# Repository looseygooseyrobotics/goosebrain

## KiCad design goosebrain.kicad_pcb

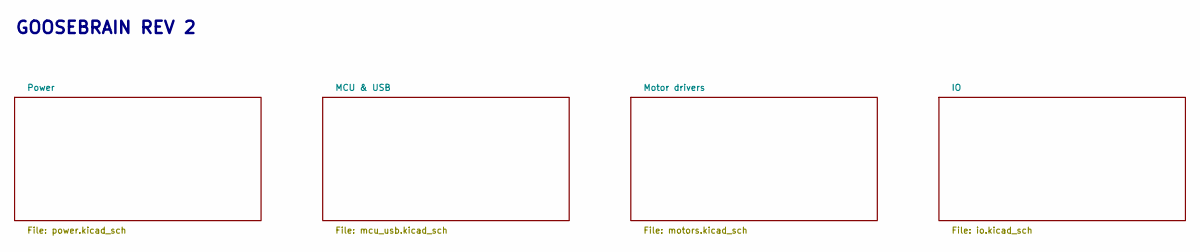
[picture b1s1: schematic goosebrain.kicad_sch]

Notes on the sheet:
GOOSEBRAIN REV 2

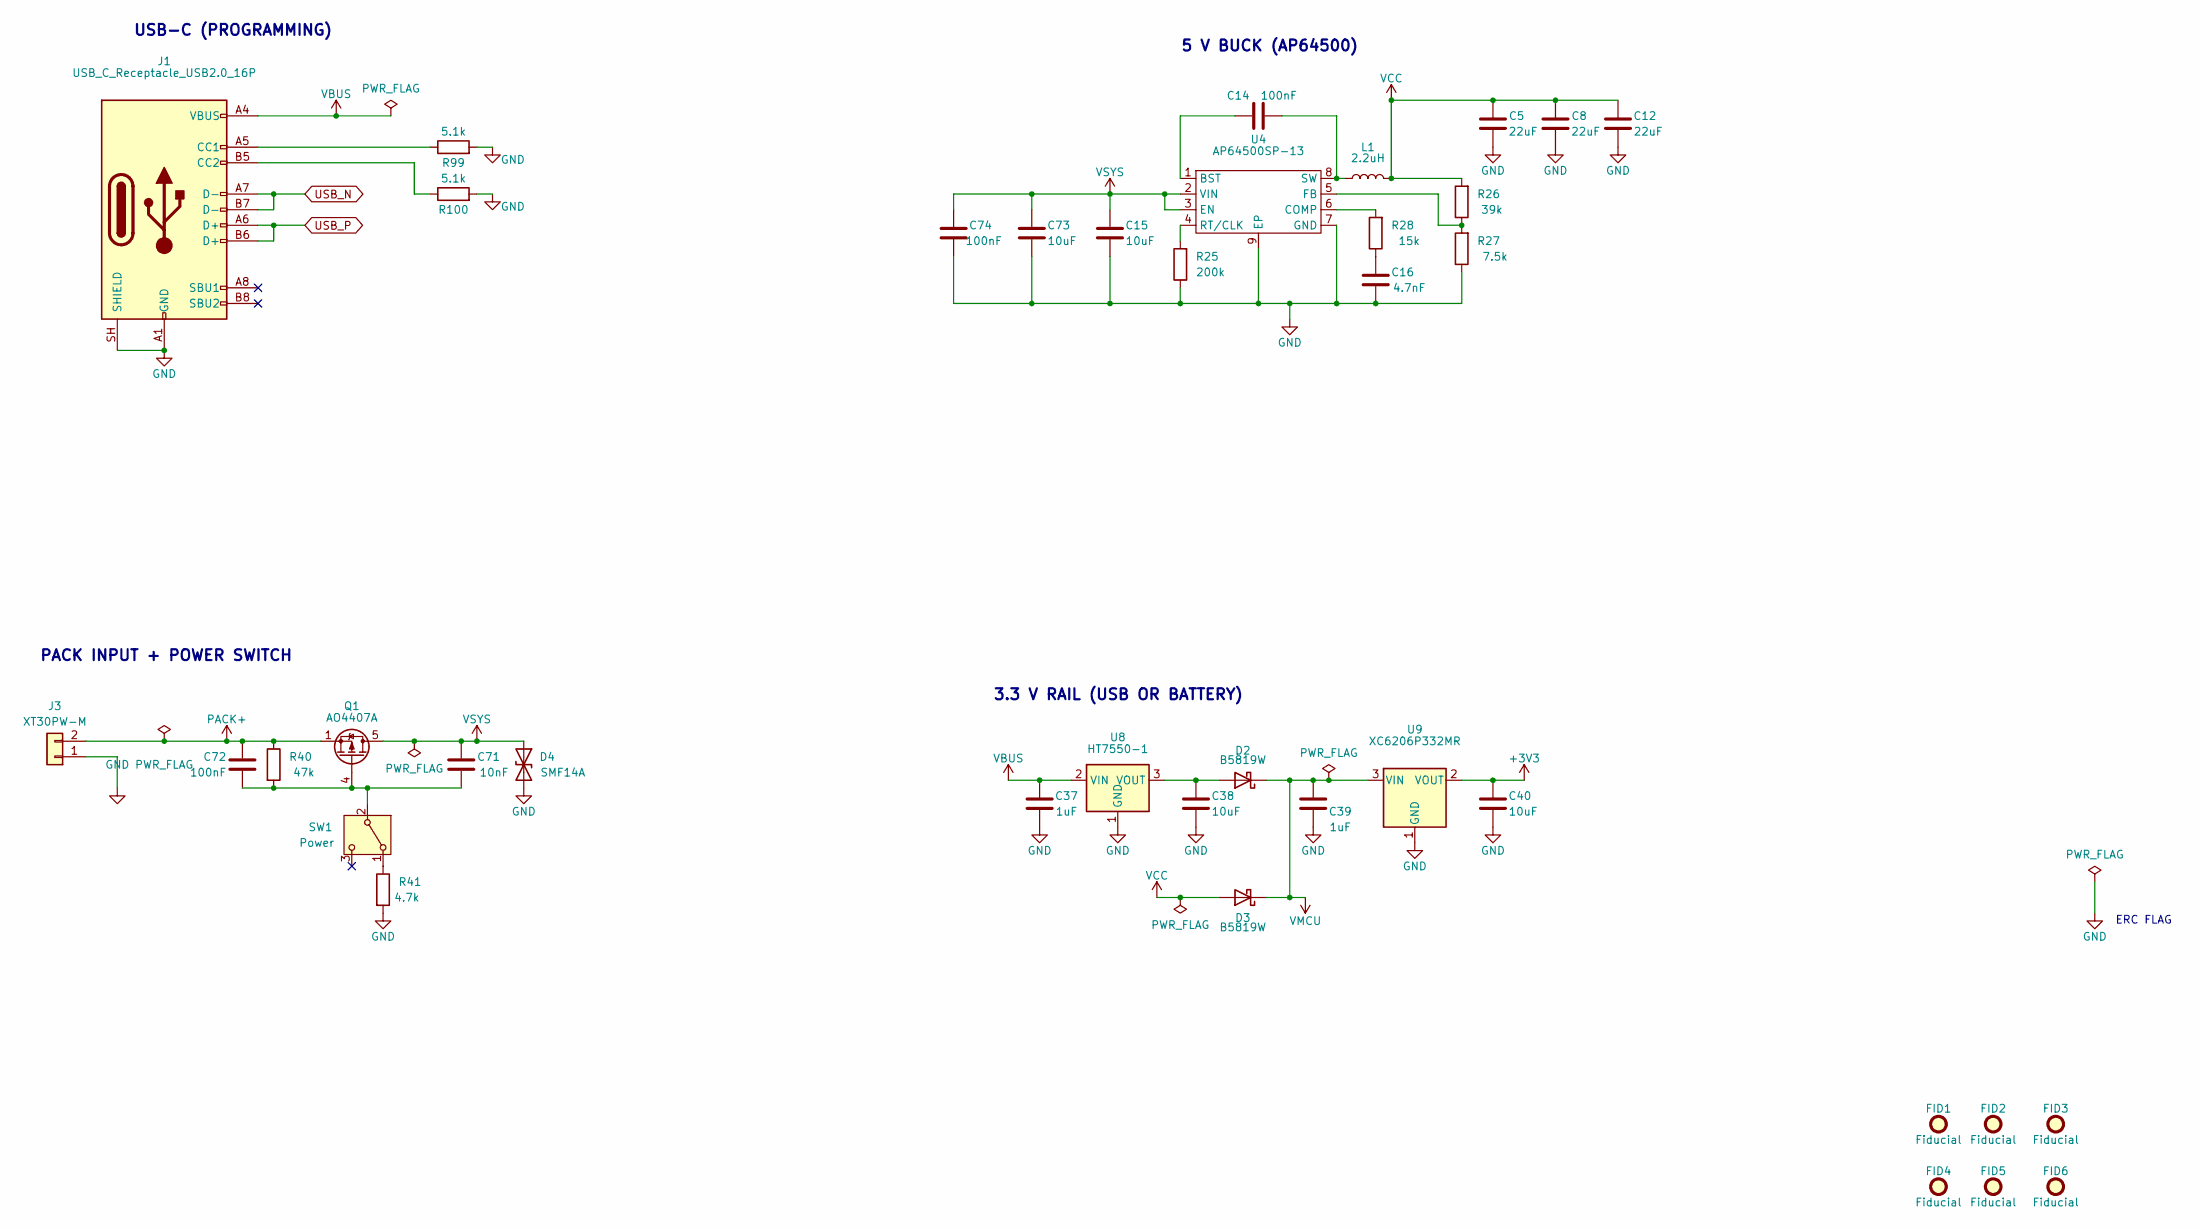
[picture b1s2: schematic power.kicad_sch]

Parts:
C5, C8, C12: 22uF; C_1206_3216Metric; MPN CL31A226KPHNNNE; LCSC Part # C5672
C14, C72: 100nF; C_0805_2012Metric; MPN CC0805KRX7R9BB104; LCSC Part # C49678
C15, C73: 10uF; C_0805_2012Metric; MPN CL21A106KAYNNNE; LCSC Part # C15850
C16: 4.7nF; C_0402_1005Metric; MPN 0402B472K500NT; LCSC Part # C1538
C37: 1uF; C_0603_1608Metric; MPN CL10A105KB8NNNC; LCSC Part # C15849
C38, C40: 10uF; C_0603_1608Metric; MPN CL10A106KP8NNNC; LCSC Part # C19702
C39: 1uF; C_0402_1005Metric; MPN CL05A105KA5NQNC; LCSC Part # C52923
C71: 10nF; C_0402_1005Metric; MPN CL05B103KB5NNNC; LCSC Part # C15195
C74: 100nF; C_0402_1005Metric; MPN CL05B104KB54PNC; LCSC Part # C307331
D2, D3: B5819W; D_SOD-123; MPN B5819W; LCSC Part # C64885
D4: SMF14A; D_SMF; MPN SMF14A; LCSC Part # C207256
FID1, FID2, FID3, FID4, FID5, FID6: Fiducial; Fiducial_1mm_Mask2mm
J1: USB_C_Receptacle_USB2.0_16P; USB_C_Receptacle_ShouHan_TYPE-C16PIN; MPN TYPE-C16PIN; LCSC Part # C393939
J3: XT30PW-M; AMASS_XT30PW-M_1x02_P2.50mm_Horizontal; MPN XT30PW-M30.G.Y; LCSC Part # C431092
L1: 2.2uH; L_ZengYi_HMS0530; MPN HMS0530-2R2M; LCSC Part # C18734448
Q1: AO4407A; SOIC-8_3.9x4.9mm_P1.27mm; MPN AO4407A; LCSC Part # C2841482
R25: 200k; R_0402_1005Metric; MPN 0402WGF2003TCE; LCSC Part # C25764
R26: 39k; R_0402_1005Metric; MPN 0402WGF3902TCE; LCSC Part # C25783
R27: 7.5k; R_0402_1005Metric; MPN 0402WGF7501TCE; LCSC Part # C25918
R28: 15k; R_0402_1005Metric; MPN 0402WGF1502TCE; LCSC Part # C25756
R40: 47k; R_0402_1005Metric; MPN 0402WGF4702TCE; LCSC Part # C25792
R41: 4.7k; R_0402_1005Metric; MPN 0402WGF4701TCE; LCSC Part # C25900
R99, R100: 5.1k; R_0402_1005Metric; MPN 0402WGF5101TCE; LCSC Part # C25905
SW1: Power; SW_SPDT_ShouHan_SK12D07VG4; MPN SK12D07VG4; LCSC Part # C393937
U4: AP64500SP-13; Diodes_SO-8EP; MPN AP64500SP-13; LCSC Part # C2070920
U8: HT7550-1; SOT-89-3; MPN HT7550-1; LCSC Part # C16106
U9: XC6206P332MR; SOT-23-3; MPN XC6206P332MR-G; LCSC Part # C5446

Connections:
+3V3: C40.1, U9.2 (VOUT); also elsewhere on the board
/Power/CC1: J1.A5 (CC1), R99.1
/Power/CC2: J1.B5 (CC2), R100.1
GND: C5.2, C8.2, C12.2, C15.1, C16.1, C37.2, C38.2, C39.2, C40.2, C73.1, C74.1, D4.2 (A2), J1.A1 (GND), J1.A12 (GND), J1.B1 (GND), J1.B12 (GND), J1.SH (SHIELD), J3.1, R25.1, R27.1, R41.2, R99.2, R100.2, U4.7 (GND), U4.9 (EP), U8.1 (GND), U9.1 (GND); also elsewhere on the board
unnamed: C16.2, R28.1
unnamed: C38.1, D2.2 (A), U8.3 (VOUT)
unnamed: C71.1, C72.2, Q1.4 (G), R40.2, SW1.2 (B)
unnamed: R41.1, SW1.1 (A)
unnamed: C14.2, U4.1 (BST)
unnamed: R28.2, U4.6 (COMP)
unnamed: R26.1, R27.2, U4.5 (FB)
unnamed: R25.2, U4.4 (RT/CLK)
unnamed: C14.1, L1.1, U4.8 (SW)
PACK+: C72.1, J3.2, Q1.1 (S), Q1.2 (S), Q1.3 (S), R40.1
VBUS: C37.1, J1.A4 (VBUS), J1.A9 (VBUS), J1.B4 (VBUS), J1.B9 (VBUS), U8.2 (VIN)
VCC: C5.1, C8.1, C12.1, D3.2 (A), L1.2, R26.2; also elsewhere on the board
VMCU: C39.1, D2.1 (K), D3.1 (K), U9.3 (VIN); also elsewhere on the board
VSYS: C15.2, C71.2, C73.2, C74.2, D4.1 (A1), Q1.5 (D), Q1.6 (D), Q1.7 (D), Q1.8 (D), U4.2 (VIN), U4.3 (EN); also elsewhere on the board

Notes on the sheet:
ERC FLAG
3.3 V RAIL (USB OR BATTERY)
5 V BUCK (AP64500)
USB-C (PROGRAMMING)
PACK INPUT + POWER SWITCH

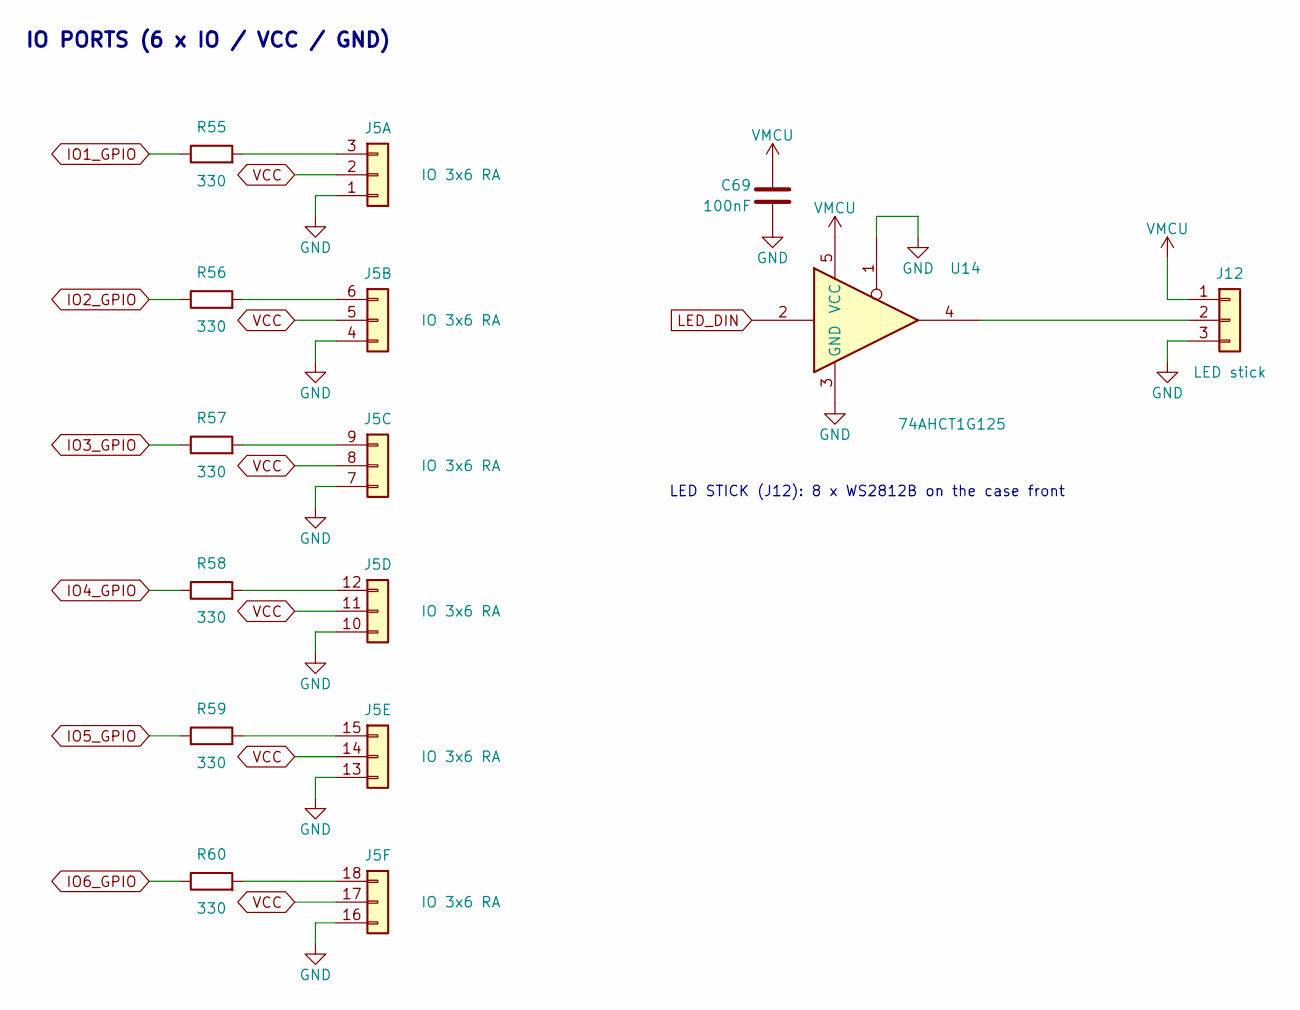
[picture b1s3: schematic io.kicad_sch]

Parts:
C69: 100nF; C_0402_1005Metric; MPN CL05B104KO5NNNC; LCSC Part # C1525
J5: IO 3x6 RA; PinHeader_3x06_P2.54mm_Horizontal_WingTAT; MPN 2011-3X06G00RB; LCSC Part # C51953246
J12: LED stick; JST_PH_B3B-PH-K_1x03_P2.00mm_Vertical; MPN B3B-PH-K-S(LF)(SN); LCSC Part # C131339
R55, R56, R57, R58, R59, R60: 330; R_0402_1005Metric; MPN 0402WGF3300TCE; LCSC Part # C25104
U14: 74AHCT1G125; SOT-23-5; MPN SN74AHCT1G125DBVR; LCSC Part # C20617903

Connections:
GND: C69.2, J5.1 (GND), J5.4 (GND), J5.7 (GND), J5.10 (GND), J5.13 (GND), J5.16 (GND), J12.3, U14.1, U14.3 (GND); also elsewhere on the board
IO1_GPIO: R55.1; also elsewhere on the board
IO2_GPIO: R56.1; also elsewhere on the board
IO3_GPIO: R57.1; also elsewhere on the board
IO4_GPIO: R58.1; also elsewhere on the board
IO5_GPIO: R59.1; also elsewhere on the board
IO6_GPIO: R60.1; also elsewhere on the board
LED_DIN: U14.2; also elsewhere on the board
unnamed: J5.3 (SIG), R55.2
unnamed: J5.6 (SIG), R56.2
unnamed: J5.9 (SIG), R57.2
unnamed: J5.12 (SIG), R58.2
unnamed: J5.15 (SIG), R59.2
unnamed: J5.18 (SIG), R60.2
unnamed: J12.2, U14.4
VCC: J5.2 (5V), J5.5 (5V), J5.8 (5V), J5.11 (5V), J5.14 (5V), J5.17 (5V); also elsewhere on the board
VMCU: C69.1, J12.1, U14.5 (VCC); also elsewhere on the board

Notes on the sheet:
LED STICK (J12): 8 x WS2812B on the case front
IO PORTS (6 x IO / VCC / GND)

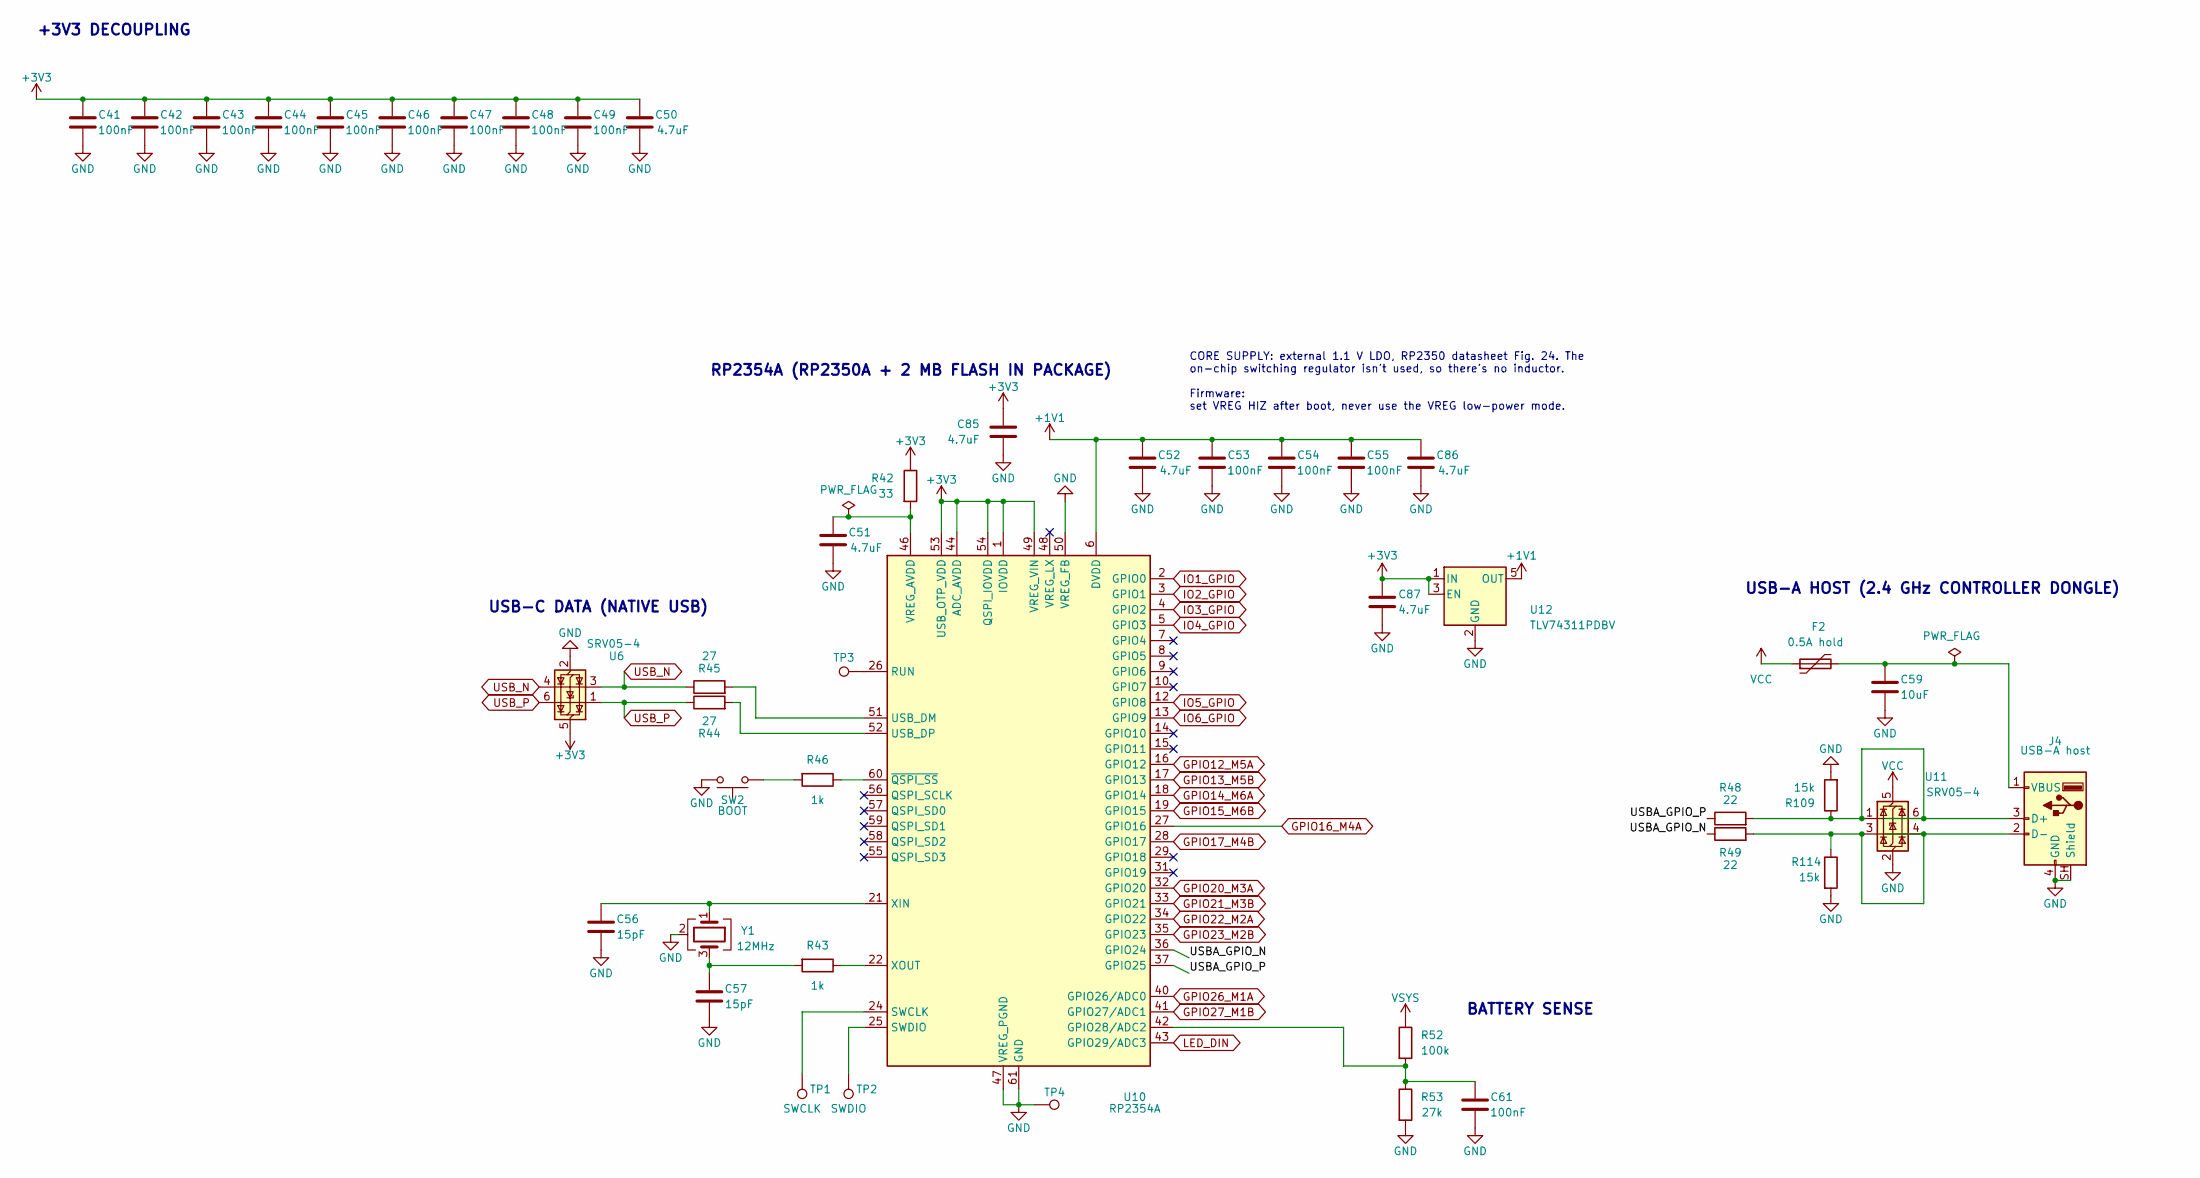
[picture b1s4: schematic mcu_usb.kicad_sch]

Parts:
C41, C42, C43, C44, C45, C46, C47, C48, C49, C53, C54, C55, C61: 100nF; C_0402_1005Metric; MPN CL05B104KO5NNNC; LCSC Part # C1525
C50, C51, C52, C85, C86, C87: 4.7uF; C_0402_1005Metric; MPN CL05A475MP5NRNC; LCSC Part # C23733
C56, C57: 15pF; C_0402_1005Metric; MPN 0402CG150J500NT; LCSC Part # C1548
C59: 10uF; C_0805_2012Metric; MPN CL21A106KAYNNNE; LCSC Part # C15850
F2: 0.5A hold; Fuse_1206_3216Metric; MPN JK-nSMD050-16; LCSC Part # C2680506
J4: USB-A host; USB_A_ShouHan_AF90_WJDG; MPN AF 90 WJDG; LCSC Part # C456018
R42: 33; R_0402_1005Metric; MPN 0402WGF330JTCE; LCSC Part # C25105
R43, R46: 1k; R_0402_1005Metric; MPN 0402WGF1001TCE; LCSC Part # C11702
R44, R45: 27; R_0603_1608Metric; MPN 0603WAF270JT5E; LCSC Part # C25190
R48, R49: 22; R_0402_1005Metric; MPN 0402WGF220JTCE; LCSC Part # C25092
R52: 100k; R_0402_1005Metric; MPN 0402WGF1003TCE; LCSC Part # C25741
R53: 27k; R_0402_1005Metric; MPN 0402WGF2702TCE; LCSC Part # C25771
R109, R114: 15k; R_0402_1005Metric; MPN 0402WGF1502TCE; LCSC Part # C25756
SW2: BOOT; SW_Push_1P1T-MP_NO_Horizontal_Alps_SKRTLAE010_JLC; MPN SKRTLAE010; LCSC Part # C110293
TP1: SWCLK; TestPoint_Pad_D1.0mm
TP2: SWDIO; TestPoint_Pad_D1.0mm
TP3: RUN; TestPoint_Pad_D1.0mm
TP4: GND; TestPoint_Pad_D1.0mm
U6, U11: SRV05-4; SOT-23-6; MPN SRV05-4; LCSC Part # C7420376
U10: RP2354A; QFN-60-1EP_7x7mm_P0.4mm_EP3.4x3.4mm; MPN RP2354A; LCSC Part # C41378174
U12: TLV74311PDBV; SOT-23-5; MPN TLV74311PDBVR; LCSC Part # C485147
Y1: 12MHz; Crystal_SMD_3225-4Pin_3.2x2.5mm; MPN ABM8-272-T3; LCSC Part # C20625731

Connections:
+1V1: C52.1, C53.1, C54.1, C55.1, C86.1, U10.6 (DVDD), U10.23 (DVDD), U10.39 (DVDD), U12.5 (OUT)
+3V3: C41.1, C42.1, C43.1, C44.1, C45.1, C46.1, C47.1, C48.1, C49.1, C50.1, C85.1, C87.1, R42.1, U6.5 (VP), U10.1 (IOVDD), U10.11 (IOVDD), U10.20 (IOVDD), U10.30 (IOVDD), U10.38 (IOVDD), U10.44 (ADC_AVDD), U10.45 (IOVDD), U10.49 (VREG_VIN), U10.53 (USB_OTP_VDD), U10.54 (QSPI_IOVDD), U12.1 (IN), U12.3 (EN); also elsewhere on the board
/MCU & USB/BAT_SENSE: C61.1, R52.2, R53.1, U10.42 (GPIO28/ADC2)
/MCU & USB/RUN: TP3.1 (1_1), U10.26 (RUN)
/MCU & USB/USBA_GPIO_N: R49.1, U10.36 (GPIO24)
/MCU & USB/USBA_GPIO_P: R48.1, U10.37 (GPIO25)
/MCU & USB/USBA_N: J4.2 (D-), R49.2, R114.1, U11.3 (IO2), U11.4 (IO3)
/MCU & USB/USBA_P: J4.3 (D+), R48.2, R109.1, U11.1 (IO1), U11.6 (IO4)
GND: C41.2, C42.2, C43.2, C44.2, C45.2, C46.2, C47.2, C48.2, C49.2, C50.2, C51.2, C52.2, C53.2, C54.2, C55.2, C56.2, C57.2, C59.2, C61.2, C85.2, C86.2, C87.2, J4.4 (GND), J4.SH (Shield), R53.2, R109.2, R114.2, SW2.2, TP4.1 (1_1), U6.2 (VN), U10.47 (VREG_PGND), U10.50 (VREG_FB), U10.61 (GND), U11.2 (VN), U12.2 (GND), Y1.2 (G), Y1.4 (G); also elsewhere on the board
GPIO12_M5A: U10.16 (GPIO12); also elsewhere on the board
GPIO13_M5B: U10.17 (GPIO13); also elsewhere on the board
GPIO14_M6A: U10.18 (GPIO14); also elsewhere on the board
GPIO15_M6B: U10.19 (GPIO15); also elsewhere on the board
GPIO16_M4A: U10.27 (GPIO16); also elsewhere on the board
GPIO17_M4B: U10.28 (GPIO17); also elsewhere on the board
GPIO20_M3A: U10.32 (GPIO20); also elsewhere on the board
GPIO21_M3B: U10.33 (GPIO21); also elsewhere on the board
GPIO22_M2A: U10.34 (GPIO22); also elsewhere on the board
GPIO23_M2B: U10.35 (GPIO23); also elsewhere on the board
GPIO26_M1A: U10.40 (GPIO26/ADC0); also elsewhere on the board
GPIO27_M1B: U10.41 (GPIO27/ADC1); also elsewhere on the board
IO1_GPIO: U10.2 (GPIO0); also elsewhere on the board
IO2_GPIO: U10.3 (GPIO1); also elsewhere on the board
IO3_GPIO: U10.4 (GPIO2); also elsewhere on the board
IO4_GPIO: U10.5 (GPIO3); also elsewhere on the board
IO5_GPIO: U10.12 (GPIO8); also elsewhere on the board
IO6_GPIO: U10.13 (GPIO9); also elsewhere on the board
LED_DIN: U10.43 (GPIO29/ADC3); also elsewhere on the board
unnamed: C57.1, R43.2, Y1.3
unnamed: C59.1, F2.2, J4.1 (VBUS)
unnamed: R46.2, SW2.1
unnamed: TP1.1 (1_1), U10.24 (SWCLK)
unnamed: TP2.1 (1_1), U10.25 (SWDIO)
unnamed: C51.1, R42.2, U10.46 (VREG_AVDD)
unnamed: C56.1, U10.21 (XIN), Y1.1
unnamed: R43.1, U10.22 (XOUT)
unnamed: R46.1, U10.60 (~QSPI_SS)
VCC: F2.1, U11.5 (VP); also elsewhere on the board
VSYS: R52.1; also elsewhere on the board

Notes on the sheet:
RP2354A (RP2350A + 2 MB FLASH IN PACKAGE)
+3V3 DECOUPLING
CORE SUPPLY: external 1.1 V LDO, RP2350 datasheet Fig. 24. The on-chip switching regulator isn't used, so there's no inductor. Firmware: set VREG HIZ after boot, never use the VREG low-power mode.
BATTERY SENSE
USB-C DATA (NATIVE USB)
USB-A HOST (2.4 GHz CONTROLLER DONGLE)

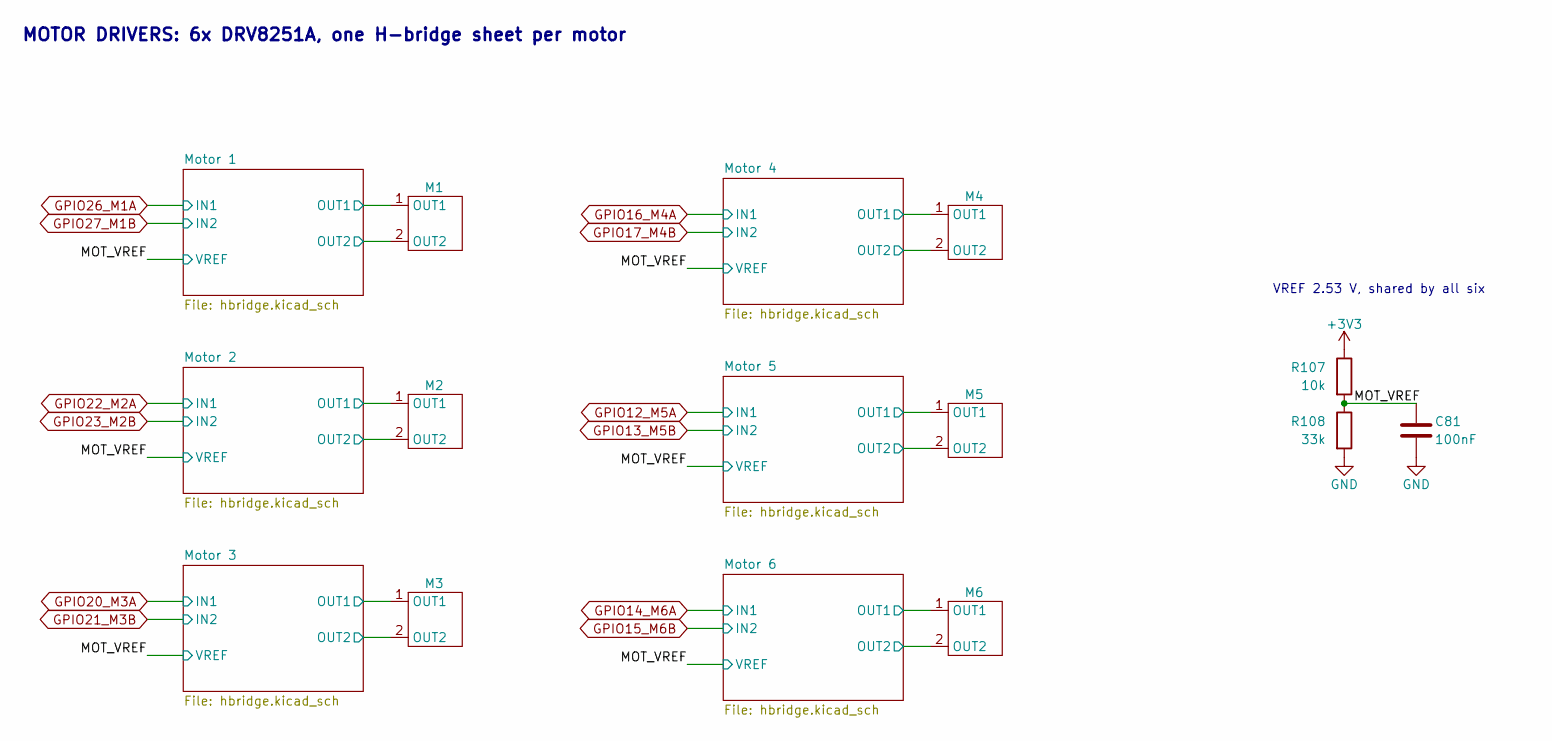
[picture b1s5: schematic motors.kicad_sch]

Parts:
C81: 100nF; C_0402_1005Metric; MPN CL05B104KO5NNNC; LCSC Part # C1525
M1, M2, M3, M4, M5, M6: JST_PH_S2B-PH-K_1x02_P2.00mm_Horizontal; MPN S2B-PH-K-S(LF)(SN); LCSC Part # C173752
R107: 10k; R_0402_1005Metric; MPN 0402WGF1002TCE; LCSC Part # C25744
R108: 33k; R_0402_1005Metric; MPN 0402WGF3302TCE; LCSC Part # C25779

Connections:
+3V3: R107.1; also elsewhere on the board
/Motor drivers/MOT_VREF: C81.1, R107.2, R108.1; also elsewhere on the board
/Motor drivers/Motor 1/OUT1: M1.1 (OUT1); also elsewhere on the board
/Motor drivers/Motor 1/OUT2: M1.2 (OUT2); also elsewhere on the board
/Motor drivers/Motor 2/OUT1: M2.1 (OUT1); also elsewhere on the board
/Motor drivers/Motor 2/OUT2: M2.2 (OUT2); also elsewhere on the board
/Motor drivers/Motor 3/OUT1: M3.1 (OUT1); also elsewhere on the board
/Motor drivers/Motor 3/OUT2: M3.2 (OUT2); also elsewhere on the board
/Motor drivers/Motor 4/OUT1: M4.1 (OUT1); also elsewhere on the board
/Motor drivers/Motor 4/OUT2: M4.2 (OUT2); also elsewhere on the board
/Motor drivers/Motor 5/OUT1: M5.1 (OUT1); also elsewhere on the board
/Motor drivers/Motor 5/OUT2: M5.2 (OUT2); also elsewhere on the board
/Motor drivers/Motor 6/OUT1: M6.1 (OUT1); also elsewhere on the board
/Motor drivers/Motor 6/OUT2: M6.2 (OUT2); also elsewhere on the board
GND: C81.2, R108.2; also elsewhere on the board

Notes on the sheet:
VREF 2.53 V, shared by all six
MOTOR DRIVERS: 6x DRV8251A, one H-bridge sheet per motor

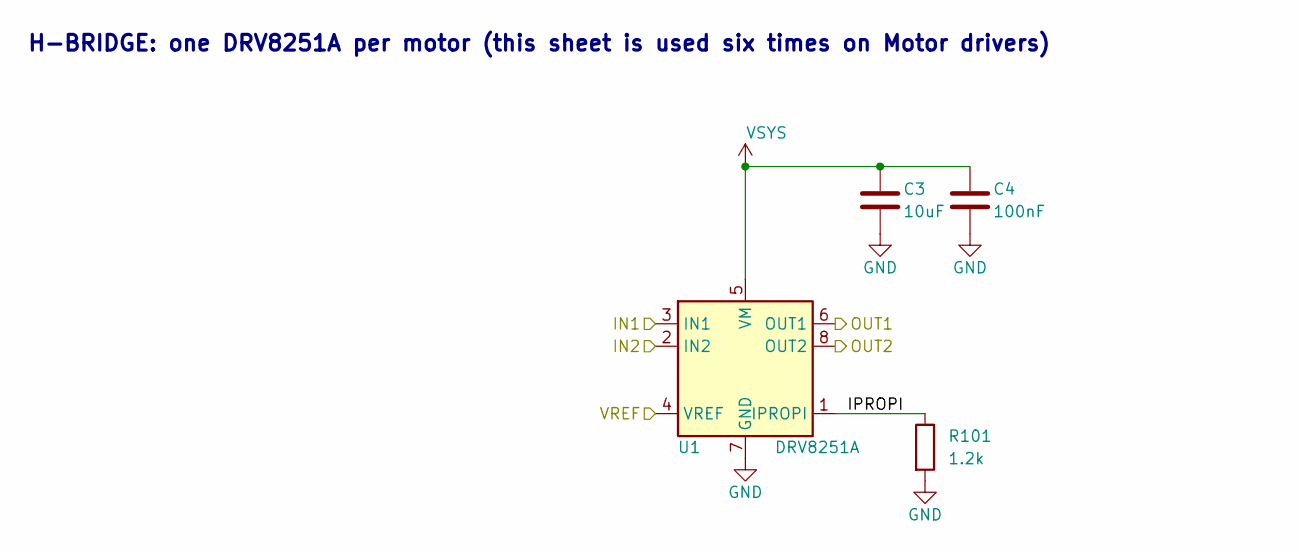
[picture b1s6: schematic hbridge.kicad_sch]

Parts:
C3: 10uF; C_0805_2012Metric; MPN CL21A106KAYNNNE; LCSC Part # C15850
C4: 100nF; C_0805_2012Metric; MPN CC0805KRX7R9BB104; LCSC Part # C49678
R101: 1.2k; R_0402_1005Metric; MPN 0402WGF1201TCE; LCSC Part # C25862
U1: DRV8251A; Texas_HTSOP-8-1EP_3.9x4.9mm_P1.27mm_EP2.95x4.9mm_Mask2.4x3.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; MPN DRV8251ADDAR; LCSC Part # C5218844

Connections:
/Motor drivers/MOT_VREF: U1.4 (VREF); also elsewhere on the board
/Motor drivers/Motor 1/IPROPI: R101.1, U1.1 (IPROPI)
/Motor drivers/Motor 1/OUT1: U1.6 (OUT1); also elsewhere on the board
/Motor drivers/Motor 1/OUT2: U1.8 (OUT2); also elsewhere on the board
GND: C3.2, C4.2, R101.2, U1.7 (GND), U1.9 (GND); also elsewhere on the board
GPIO26_M1A: U1.3 (IN1); also elsewhere on the board
GPIO27_M1B: U1.2 (IN2); also elsewhere on the board
VSYS: C3.1, C4.1, U1.5 (VM); also elsewhere on the board

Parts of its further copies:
C6, C10, C75, C77, C79: 10uF; C_0805_2012Metric; MPN CL21A106KAYNNNE; LCSC Part # C15850
C7, C11, C76, C78, C80: 100nF; C_0805_2012Metric; MPN CC0805KRX7R9BB104; LCSC Part # C49678
R102, R103, R104, R105, R106: 1.2k; R_0402_1005Metric; MPN 0402WGF1201TCE; LCSC Part # C25862
U2, U3, U15, U16, U17: DRV8251A; Texas_HTSOP-8-1EP_3.9x4.9mm_P1.27mm_EP2.95x4.9mm_Mask2.4x3.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; MPN DRV8251ADDAR; LCSC Part # C5218844

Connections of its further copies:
/Motor drivers/MOT_VREF: U2.4 (VREF), U3.4 (VREF), U15.4 (VREF), U16.4 (VREF), U17.4 (VREF); also elsewhere on the board
/Motor drivers/Motor 2/IPROPI: R102.1, U15.1 (IPROPI)
/Motor drivers/Motor 2/OUT1: U15.6 (OUT1); also elsewhere on the board
/Motor drivers/Motor 2/OUT2: U15.8 (OUT2); also elsewhere on the board
/Motor drivers/Motor 3/IPROPI: R103.1, U2.1 (IPROPI)
/Motor drivers/Motor 3/OUT1: U2.6 (OUT1); also elsewhere on the board
/Motor drivers/Motor 3/OUT2: U2.8 (OUT2); also elsewhere on the board
/Motor drivers/Motor 4/IPROPI: R104.1, U16.1 (IPROPI)
/Motor drivers/Motor 4/OUT1: U16.6 (OUT1); also elsewhere on the board
/Motor drivers/Motor 4/OUT2: U16.8 (OUT2); also elsewhere on the board
/Motor drivers/Motor 5/IPROPI: R105.1, U3.1 (IPROPI)
/Motor drivers/Motor 5/OUT1: U3.6 (OUT1); also elsewhere on the board
/Motor drivers/Motor 5/OUT2: U3.8 (OUT2); also elsewhere on the board
/Motor drivers/Motor 6/IPROPI: R106.1, U17.1 (IPROPI)
/Motor drivers/Motor 6/OUT1: U17.6 (OUT1); also elsewhere on the board
/Motor drivers/Motor 6/OUT2: U17.8 (OUT2); also elsewhere on the board
GND: C6.2, C7.2, C10.2, C11.2, C75.2, C76.2, C77.2, C78.2, C79.2, C80.2, R102.2, R103.2, R104.2, R105.2, R106.2, U2.7 (GND), U2.9 (GND), U3.7 (GND), U3.9 (GND), U15.7 (GND), U15.9 (GND), U16.7 (GND), U16.9 (GND), U17.7 (GND), U17.9 (GND); also elsewhere on the board
GPIO12_M5A: U3.3 (IN1); also elsewhere on the board
GPIO13_M5B: U3.2 (IN2); also elsewhere on the board
GPIO14_M6A: U17.3 (IN1); also elsewhere on the board
GPIO15_M6B: U17.2 (IN2); also elsewhere on the board
GPIO16_M4A: U16.3 (IN1); also elsewhere on the board
GPIO17_M4B: U16.2 (IN2); also elsewhere on the board
GPIO20_M3A: U2.3 (IN1); also elsewhere on the board
GPIO21_M3B: U2.2 (IN2); also elsewhere on the board
GPIO22_M2A: U15.3 (IN1); also elsewhere on the board
GPIO23_M2B: U15.2 (IN2); also elsewhere on the board
VSYS: C6.1, C7.1, C10.1, C11.1, C75.1, C76.1, C77.1, C78.1, C79.1, C80.1, U2.5 (VM), U3.5 (VM), U15.5 (VM), U16.5 (VM), U17.5 (VM); also elsewhere on the board

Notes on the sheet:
H-BRIDGE: one DRV8251A per motor (this sheet is used six times on Motor drivers)

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
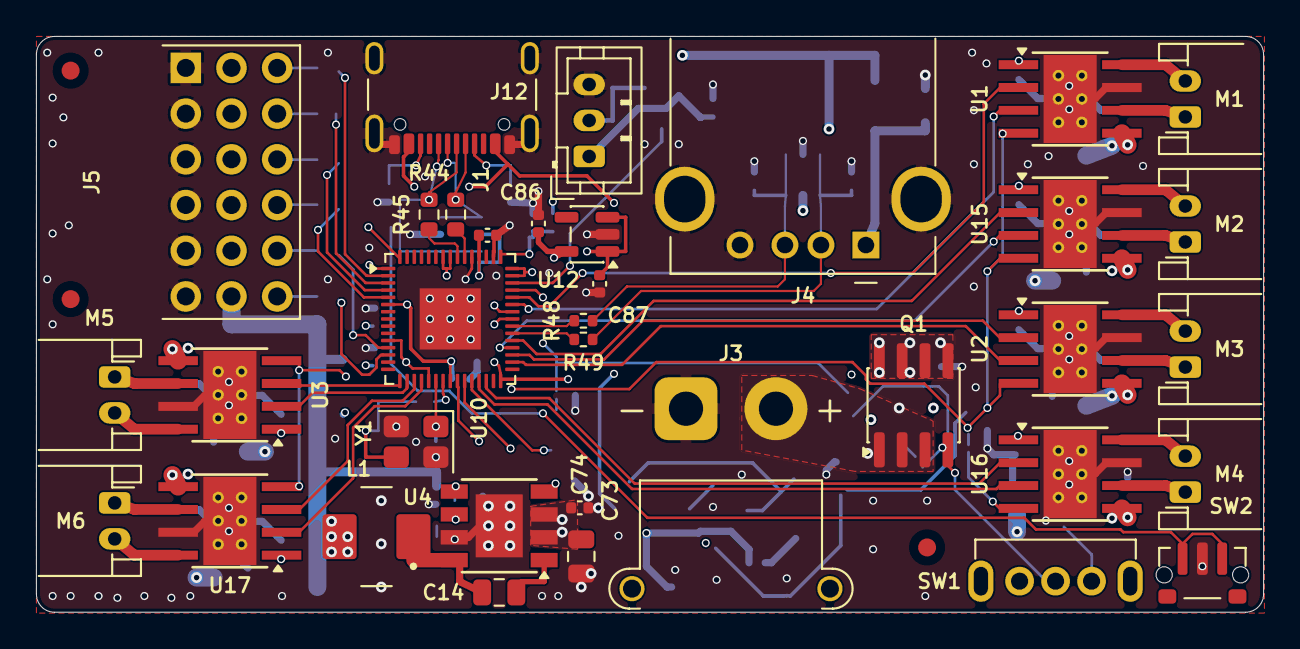
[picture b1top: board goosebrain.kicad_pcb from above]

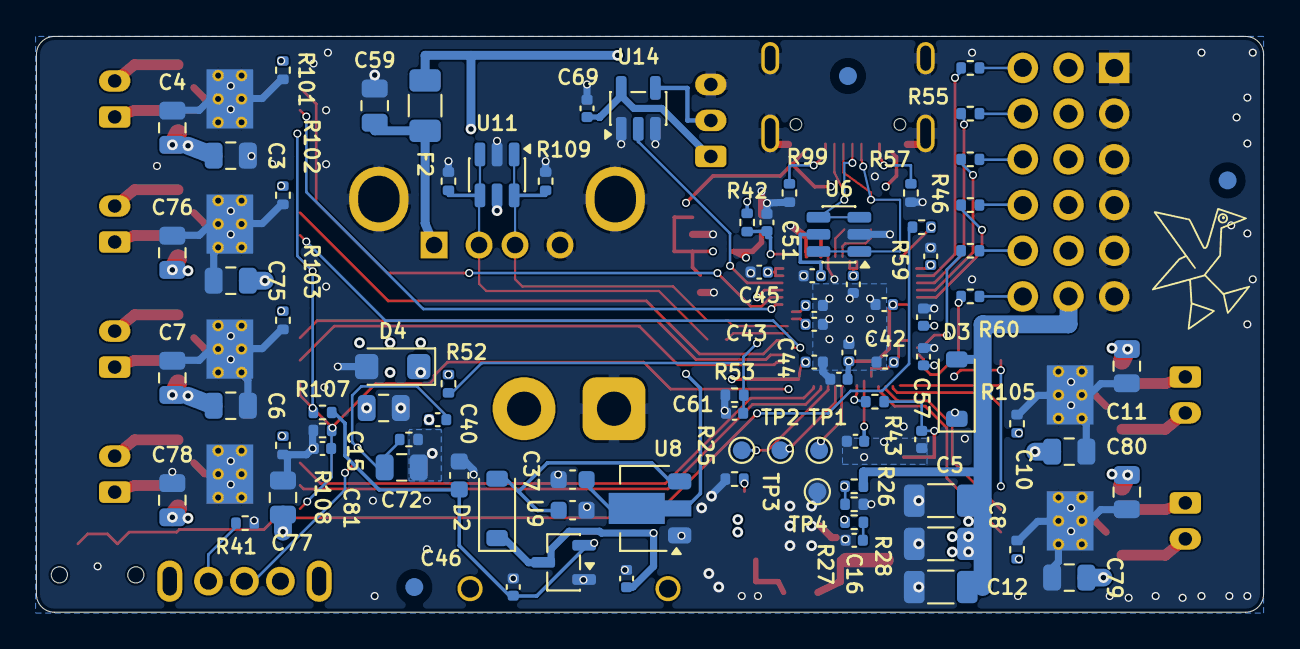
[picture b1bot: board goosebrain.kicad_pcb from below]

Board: 6 copper layers, 68.2 x 32.0 mm, 127 parts (89 on the bottom side), 83 nets.
